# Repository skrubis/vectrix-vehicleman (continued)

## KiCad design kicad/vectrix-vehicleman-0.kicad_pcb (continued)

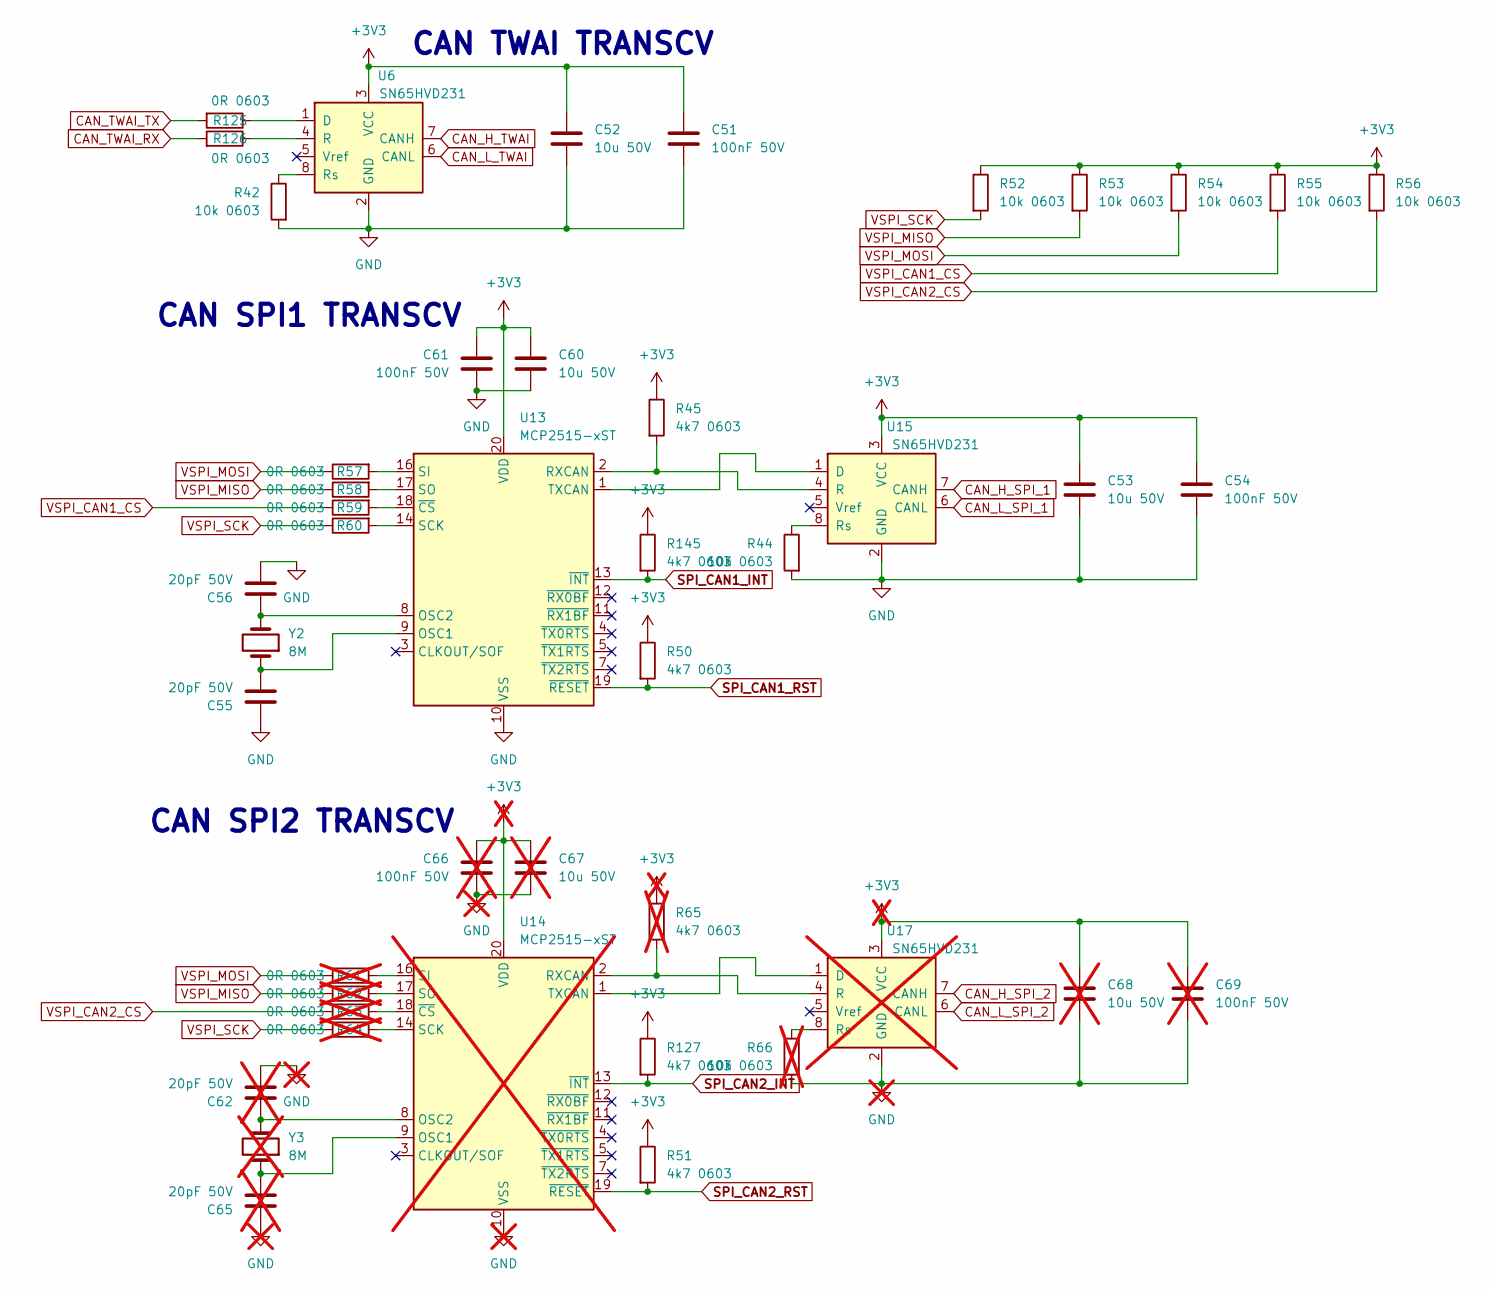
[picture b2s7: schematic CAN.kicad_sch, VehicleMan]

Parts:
C51, C54, C61: 100nF 50V; C_0603_1608Metric; LCSC C14663
C52, C53, C60: 10u 50V; C_1206_3216Metric; LCSC C13585
C55, C56: 20pF 50V; C_0603_1608Metric; LCSC C105621
C62, C65: 20pF 50V; C_0603_1608Metric; LCSC C105621; not fitted
C66, C69: 100nF 50V; C_0603_1608Metric; LCSC C14663; not fitted
C67, C68: 10u 50V; C_1206_3216Metric; LCSC C13585; not fitted
R42, R44, R52, R53, R54, R55, R56: 10k 0603; R_0603_1608Metric; LCSC C2930027
R45, R50, R51, R127, R145: 4k7 0603; R_0603_1608Metric; LCSC C99782
R57, R58, R59, R60, R125, R126: 0R 0603; R_0603_1608Metric; LCSC C21189
R61, R62, R63, R64: 0R 0603; R_0603_1608Metric; LCSC C21189; not fitted
R65: 4k7 0603; R_0603_1608Metric; LCSC C99782; not fitted
R66: 10k 0603; R_0603_1608Metric; LCSC C2930027; not fitted
U6, U15: SN65HVD231; SOIC-8_3.9x4.9mm_P1.27mm; LCSC C12084
U13: MCP2515-xST; TSSOP-20_4.4x6.5mm_P0.65mm; LCSC C185941
U14: MCP2515-xST; TSSOP-20_4.4x6.5mm_P0.65mm; LCSC C185941; not fitted
U17: SN65HVD231; SOIC-8_3.9x4.9mm_P1.27mm; LCSC C12084; not fitted
Y2: 8M; Crystal_SMD_HC49-SD
Y3: 8M; Crystal_SMD_HC49-SD; not fitted

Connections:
+3V3: C51.1, C52.1, C53.1, C54.1, C60.1, C61.1, C66.1, C67.1, C68.1, C69.1, R45.1, R50.1, R51.1, R52.1, R53.1, R54.1, R55.1, R56.1, R65.1, R127.1, R145.1, U6.3 (VCC), U13.20 (VDD), U14.20 (VDD), U15.3 (VCC), U17.3 (VCC); also elsewhere on the board
CAN_H_SPI_1: U15.7 (CANH); also elsewhere on the board
CAN_H_SPI_2: U17.7 (CANH); also elsewhere on the board
CAN_H_TWAI: U6.7 (CANH); also elsewhere on the board
CAN_L_SPI_1: U15.6 (CANL); also elsewhere on the board
CAN_L_SPI_2: U17.6 (CANL); also elsewhere on the board
CAN_L_TWAI: U6.6 (CANL); also elsewhere on the board
CAN_TWAI_RX: R126.2; also elsewhere on the board
CAN_TWAI_TX: R125.2; also elsewhere on the board
GND: C51.2, C52.2, C53.2, C54.2, C55.1, C56.2, C60.2, C61.2, C62.2, C65.1, C66.2, C67.2, C68.2, C69.2, R42.2, R44.2, R66.2, U6.2 (GND), U13.10 (VSS), U14.10 (VSS), U15.2 (GND), U17.2 (GND); also elsewhere on the board
unnamed: R125.1, U6.1 (D)
unnamed: R126.1, U6.4 (R)
unnamed: R42.1, U6.8 (Rs)
unnamed: C55.2, U13.9 (OSC1), Y2.1
unnamed: C56.1, U13.8 (OSC2), Y2.2
unnamed: R45.2, U13.2 (RXCAN), U15.4 (R)
unnamed: R60.2, U13.14 (SCK)
unnamed: R57.2, U13.16 (SI)
unnamed: R58.2, U13.17 (SO)
unnamed: U13.1 (TXCAN), U15.1 (D)
unnamed: R59.2, U13.18 (~CS)
unnamed: C65.2, U14.9 (OSC1), Y3.1
unnamed: C62.1, U14.8 (OSC2), Y3.2
unnamed: R65.2, U14.2 (RXCAN), U17.4 (R)
unnamed: R64.2, U14.14 (SCK)
unnamed: R61.2, U14.16 (SI)
unnamed: R62.2, U14.17 (SO)
unnamed: U14.1 (TXCAN), U17.1 (D)
unnamed: R63.2, U14.18 (~CS)
unnamed: R44.1, U15.8 (Rs)
unnamed: R66.1, U17.8 (Rs)
SPI_CAN1_INT: R145.2, U13.13 (~INT); also elsewhere on the board
SPI_CAN1_RST: R50.2, U13.19 (~RESET); also elsewhere on the board
SPI_CAN2_INT: R127.2, U14.13 (~INT); also elsewhere on the board
SPI_CAN2_RST: R51.2, U14.19 (~RESET); also elsewhere on the board
VSPI_CAN1_CS: R55.2, R59.1; also elsewhere on the board
VSPI_CAN2_CS: R56.2, R63.1; also elsewhere on the board
VSPI_MISO: R53.2, R58.1, R62.1; also elsewhere on the board
VSPI_MOSI: R54.2, R57.1, R61.1; also elsewhere on the board
VSPI_SCK: R52.2, R60.1, R64.1; also elsewhere on the board

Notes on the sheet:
CAN SPI2 TRANSCV
CAN SPI1 TRANSCV
CAN TWAI TRANSCV

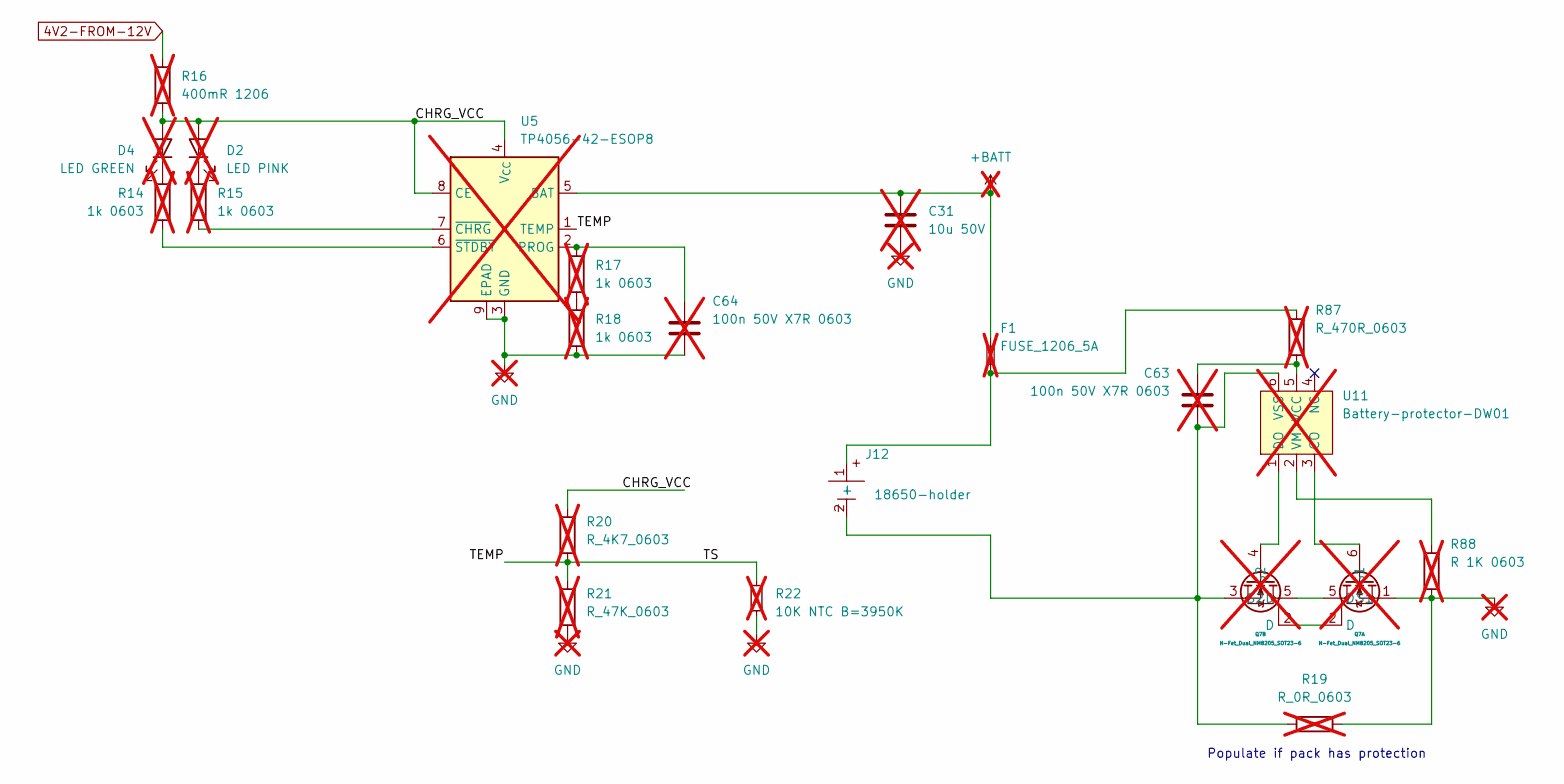
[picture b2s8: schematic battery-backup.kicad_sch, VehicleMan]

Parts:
C31: 10u 50V; C_1206_3216Metric; LCSC C13585; not fitted
C63, C64: 100n 50V X7R 0603; C_0603_1608Metric; LCSC C314282; not fitted
D2: LED PINK; LED_0805_2012Metric; LCSC C965821; not fitted
D4: LED GREEN; LED_0805_2012Metric; LCSC C5875740; not fitted
F1: FUSE_1206_5A; Fuse_1206_3216Metric; LCSC C883136; not fitted
J12: 18650-holder; C5290175-18650-holder; LCSC C5290175
Q7: N-Fet_Dual_NM8205_SOT23-6; SOT-23-6; LCSC C5156806; not fitted
R14, R15, R17, R18: 1k 0603; R_0603_1608Metric; LCSC C2907113; not fitted
R16: 400mR 1206; R_1206_3216Metric; LCSC C912792; not fitted
R19: R_0R_0603; R_0603_1608Metric; LCSC C2907080; not fitted
R20: R_4K7_0603; R_0603_1608Metric; LCSC C23162; not fitted
R21: R_47K_0603; R_0603_1608Metric; LCSC C2907173; not fitted
R22: 10K NTC B=3950K; R_0603_1608Metric; LCSC C279936; not fitted
R87: R_470R_0603; R_0603_1608Metric; LCSC C2907172; not fitted
R88: R 1K 0603; R_0603_1608Metric; LCSC C25585; not fitted
U5: TP4056-42-ESOP8; SOIC-8-1EP_3.9x4.9mm_P1.27mm_EP2.41x3.3mm_ThermalVias; not fitted
U11: Battery-protector-DW01; SOT-23-6; LCSC C917079; not fitted

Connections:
4V2-FROM-12V: R16.1; also elsewhere on the board
+BATT: C31.1, F1.2, U5.5 (BAT); also elsewhere on the board
/Battery/CHRG_VCC: D2.2 (A), D4.2 (A), R16.2, R20.1, U5.4 (V_{CC}), U5.8 (CE)
/Battery/TEMP: R20.2, R21.1, R22.1, U5.1 (TEMP)
GND: C31.2, C64.2, Q7.1 (S1), R18.2, R19.2, R21.2, R22.2, R88.2, U5.3 (GND), U5.9 (EPAD); also elsewhere on the board
unnamed: D2.1 (K), R15.1
unnamed: D4.1 (K), R14.1
unnamed: F1.1, J12.1 (+), R87.1
unnamed: C63.2, J12.2 (-), Q7.3 (S2), R19.1, U11.6 (VSS)
unnamed: Q7.6 (G1), U11.3 (CO)
unnamed: Q7.4 (G2), U11.1 (DO)
unnamed: R17.2, R18.1
unnamed: C64.1, R17.1, U5.2 (PROG)
unnamed: R15.2, U5.7 (~CHRG)
unnamed: R14.2, U5.6 (~STDBY)
unnamed: C63.1, R87.2, U11.5 (VCC)
unnamed: R88.1, U11.2 (VM)

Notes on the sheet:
Populate if pack has protection

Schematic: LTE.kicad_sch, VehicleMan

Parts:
C30, C71, C90, C94: 10u 50V; C_1206_3216Metric; LCSC C13585
C70, C100: Tant 47u 17V; CP_EIA-3528-12_Kemet-T; LCSC C136751
C79, C80, C81: 33pF 0603; C_0603_1608Metric; LCSC C107047
C87, C88, C89, C98: 100nF 50V; C_0603_1608Metric; LCSC C14663
C93, C95: 33pF 0402; C_0402_1005Metric; LCSC C1562; not fitted
C96: 33pF 0402; C_0402_1005Metric; LCSC C1562
D1: TPESD1P0RFW; SOT-323_SC-70; LCSC C521956
D18: LED GREEN; LED_0805_2012Metric; LCSC C5875740
D19: LED PINK; LED_0805_2012Metric; LCSC C965821
D26: PESD5V0L4UG; SOT-353_SC-70-5; LCSC C5116450
FB4, FB5: FB_100R_2.5A; L_0603_1608Metric; LCSC C96995
J8: SIM_Card_Shielded; nanoSIM_Hinged_CUI_NSIM-2-C; LCSC C266890
J10: GPS U.FL; U.FL_Hirose_U.FL-R-SMT-1_Vertical; LCSC C496552
J11: LTE U.FL; U.FL_Hirose_U.FL-R-SMT-1_Vertical; LCSC C496552
L1: 47nH; L_0402_1005Metric; LCSC C97998
L6, L7: 27nH; L_0402_1005Metric; LCSC C12669; not fitted
Q12, Q13, Q14, Q15, Q18: MMBT3904; SOT-23
R8, R96, R97, R104: R_27R_0603; R_0603_1608Metric; LCSC C101313
R43, R67: 1k 0603; R_0603_1608Metric; LCSC C2907113
R70, R71, R124: 100k 0603; R_0603_1608Metric; LCSC C14675
R106: 0R 0603; R_0603_1608Metric; LCSC C21189; not fitted
R107, R115, R116, R117, R119, R120, R123, R130, R131, R133: 4k7 0603; R_0603_1608Metric; LCSC C99782
R118, R121, R122, R132: 0R 0603; R_0603_1608Metric; LCSC C21189
R128, R129, R143: 0R 0402; R_0402_1005Metric; LCSC C106231
R134, R135: 4k7 0603; R_0603_1608Metric; LCSC C99782; not fitted
R144: 10R 0402; R_0402_1005Metric; LCSC C22859
TP1, TP2, TP3: TestPoint; TestPoint_Pad_D1.0mm; not fitted
U18: SIM7070G; LCSC C2892847
U23: ME6217C33M5G; SOT-23-5; LCSC C427602

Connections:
+1V8: C94.1, C98.1, R115.1, R116.1, R117.1, R119.1, R120.1, R123.1, R135.2, U18.15 (VDD_EXT)
+3V3: R70.1, R71.1, R106.2, R107.1, R133.1; also elsewhere on the board
/LTE/GNSS_ANT: L6.1, R143.2, U18.53 (GNSS_ANT)
/LTE/GPS_VCC: C71.1, C88.1, R144.2, U23.5 (V_{OUT})
/LTE/LTE_ANT: R129.2, U18.60 (RF_ANT)
/LTE/LTE_GPIO5: Q18.2 (E), R134.2, R135.1, U18.48 (GPIO5/SPI_CS)
/LTE/POWERKEY: Q15.3 (C), R132.2
/LTE/SIM_CLK: C79.1, R97.2, U18.32 (SIM_CLK)
/LTE/SIM_DATA: R104.2, U18.31 (SIM_DATA)
/LTE/SIM_RST: C80.1, R96.2, U18.33 (SIM_RST)
/LTE/SIM_VDD: R8.2, U18.30 (SIM_VDD)
/LTE/UART1_DTR: Q14.3 (C), R118.2, R120.2
/LTE/UART1_RXD: Q13.3 (C), R117.2, R121.2
/LTE/UART1_TXD: Q12.2 (E), R122.2
GND: C30.2, C70.2, C71.2, C79.2, C80.2, C81.2, C87.2, C88.2, C89.2, C90.2, C93.1, C94.2, C95.1, C98.2, C100.2, D1.3 (A), D26.2 (A), J8.5 (GND), J8.SH, J10.2 (Ext), J11.2 (Ext), L6.2, L7.2, Q15.2 (E), R43.2, R67.2, R124.2, R130.1, R134.1, U18.2 (GND), U18.17 (GND), U18.18 (GND), U18.29 (GND), U18.39 (GND), U18.45 (GND), U18.46 (GND), U18.54 (GND), U18.58 (GND), U18.59 (GND), U18.61 (GND), U18.62 (GND), U18.63 (GND), U18.64 (GND), U18.65 (GND), U23.2 (V_{SS}); also elsewhere on the board
GPS_LDO_EN: R124.1, U23.3 (CE); also elsewhere on the board
LTE_DTR: Q14.2 (E), R71.2; also elsewhere on the board
LTE_GPIO5_HV: Q18.3 (C), R133.2; also elsewhere on the board
LTE_POWERKEY: R131.1; also elsewhere on the board
LTE_RX: Q13.2 (E), R70.2; also elsewhere on the board
LTE_TX: Q12.3 (C), R107.2; also elsewhere on the board
LTE_USB_VBUS_DET: U18.24 (USB_VBUS); also elsewhere on the board
unnamed: C93.2, R128.2, R129.1
unnamed: C96.2, L7.1, R143.1
unnamed: C30.1, C70.1, C87.1, C100.1, FB4.1, R106.1, U18.55 (VBAT), U18.56 (VBAT), U18.57 (VBAT)
unnamed: D18.2 (A), U18.66 (STATUS)
unnamed: D18.1 (K), R43.1
unnamed: D19.2 (A), U18.52 (NETLIGHT)
unnamed: D19.1 (K), R67.1
unnamed: D26.1 (K1), J8.2 (RST), R96.1
unnamed: D26.3 (K2), J8.3 (CLK), R97.1
unnamed: C81.1, D26.4 (K3), J8.7 (I/O), R104.1
unnamed: D26.5 (K4), J8.1 (VCC), R8.1
unnamed: C96.1, J10.1 (In), L1.1
unnamed: C95.2, D1.1 (K), D1.2 (K), J11.1 (In), R128.1
unnamed: L1.2, R144.1
unnamed: Q12.1 (B), R115.2
unnamed: Q13.1 (B), R116.2
unnamed: Q14.1 (B), R119.2
unnamed: Q15.1 (B), R130.2, R131.2
unnamed: Q18.1 (B), R123.2
unnamed: TP1.1, U18.6 (BOOT_CFG)
unnamed: TP2.1, U18.22 (DEBUG_RXD)
unnamed: TP3.1, U18.23 (DEBUG_TXD)
unnamed: R132.1, U18.1 (PWRKEY)
unnamed: R118.1, U18.3 (UART1_DTR)
unnamed: R121.1, U18.10 (UART1_RXD)
unnamed: R122.1, U18.9 (UART1_TXD)
unnamed: C89.1, C90.1, FB5.2, U23.1 (V_{IN})
USB_LTE_DN: U18.28 (USB_DM); also elsewhere on the board
USB_LTE_DP: U18.27 (USB_DP); also elsewhere on the board
VBUS: FB4.2, FB5.1; also elsewhere on the board

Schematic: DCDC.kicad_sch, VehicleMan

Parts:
C17, C18, C97, C99: 10u 50V; C_1206_3216Metric; LCSC C13585
C22, C23, C25, C32, C38: 100nF 50V; C_0603_1608Metric; LCSC C14663
C26, C29, C74, C82, C83, C91, C92: 10u 50V; C_1206_3216Metric; LCSC C13585; not fitted
C27, C28, C72, C73, C84: 100nF 50V; C_0603_1608Metric; LCSC C14663; not fitted
C37: 100uF 25V; CP_Elec_6.3x7.7; LCSC C2918360
C75: 100uF 25V; CP_Elec_6.3x7.7; LCSC C2918360; not fitted
D8: SMAJ18A; D_SMA
D9, D20, D41: Schottky 40V 10A; TO-277B; LCSC C2988031; not fitted
D21: D_Schottky_3A_40V; D_SMA; LCSC C2758580; not fitted
F9: Polyfuse 2A; Fuse_2920_7451Metric; LCSC C6165181
F16: Polyfuse 250V .4A; Fuse_Bourns_MF-RHT200; LCSC C693579
FB3: FB_100R_2.5A; L_0603_1608Metric; LCSC C96995; not fitted
L2: Inductor_3.3uH_4.7A_shielded; L_7.3x7.3_H4.5; LCSC C216194; not fitted
L3: 5.6uH 5.5A; L_KOHERelec_MDA7030; LCSC C475914
L4: 1uH 6A; L_APV_APH0412; LCSC C167203; not fitted
L5: 1uH 6A; L_APV_APH0412; LCSC C167203
Q3: AO3400A; SOT-23; LCSC C347475; not fitted
Q6, Q8: PMOS_30V_5.5A; SOT-23; LCSC C105162; not fitted
R5: 42.2k 0603; R_0603_1608Metric; LCSC C5126245
R6: 10k 0603; R_0603_1608Metric; LCSC C2930027
R10, R12, R13, R113, R114: 100k 0603; R_0603_1608Metric; LCSC C14675; not fitted
R11: 604k 0603; R_0603_1608Metric; LCSC C2933246; not fitted
R23: 100k 0603; R_0603_1608Metric; LCSC C14675
R24: 453k 0603; R_0603_1608Metric; LCSC C27009
R68: R_47K_0603; R_0603_1608Metric; LCSC C2907173; not fitted
R69: 10k 0603; R_0603_1608Metric; LCSC C2930027; not fitted
R108, R109, R110, R111: 0R 0603; R_0603_1608Metric; LCSC C21189
U2: TPS61022; Texas_RWU0007A_VQFN-7_2x2mm_P0.5mm; not fitted
U3: TPS62A02DRL; SOT-563
U4: TPS563300; SOT-583-8; LCSC C5219249
U7: GigaESC TL494OC 2.1.0
U19: BOOSTER_2A_12V_MAX_FP6291LR-G1; SOT-23-6; LCSC C18701; not fitted

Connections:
4V2-FROM-12V: C25.1, C97.1, C99.1, L3.2, Q6.3 (D), R5.1, R108.2, R109.2; also elsewhere on the board
4V2-FROM-BAT: C72.1, C91.1, C92.1, Q3.1 (G), Q6.1 (G), Q8.3 (D), R11.1, R12.2, U2.3 (VOUT)
12V_BATT: D20.1 (A), D20.2 (A), FB3.2
12V_HV: D41.1 (A), D41.2 (A), F9.1
+3V3: C37.1, C38.1, L5.2, R24.1; also elsewhere on the board
+12P: D9.1 (A), D9.2 (A), R110.1, R111.1; also elsewhere on the board
+12V: C17.1, C22.1, D9.3 (K), D20.3 (K), D41.3 (K), R110.2, R111.2, U4.3 (VIN); also elsewhere on the board
+BATT: C26.1, C27.1, L4.1, U2.5 (EN), U2.7 (VIN); also elsewhere on the board
GND: C17.2, C18.2, C22.2, C25.2, C26.2, C27.2, C28.2, C29.2, C32.2, C37.2, C38.2, C72.2, C73.2, C74.2, C75.2, C82.2, C83.2, C84.2, C91.2, C92.2, C97.2, C99.2, D8.2 (A2), Q3.2 (S), R6.2, R10.2, R12.1, R23.2, R68.2, R69.2, U2.1 (GND), U2.6 (MODE), U3.1 (GND), U3.6 (PG), U4.4 (GND), U7.3 (GND), U19.2 (GND); also elsewhere on the board
HV+: F16.1; also elsewhere on the board
unnamed: D8.1 (A1), F9.2, U7.1 (+12V)
unnamed: D21.2 (A), L2.2, U19.1 (LX)
unnamed: C73.1, C74.1, C75.1, D21.1 (K), FB3.1, R113.1
unnamed: Q3.3 (D), Q8.1 (G), R13.1
unnamed: R113.2, R114.1
unnamed: R10.1, R11.2, U2.4 (FB)
unnamed: L4.2, U2.2 (SW)
unnamed: R23.1, R24.2, U3.5 (FB)
unnamed: L5.1, U3.2 (SW)
unnamed: C23.1, U4.6 (BST)
unnamed: R5.2, R6.1, U4.8 (FB)
unnamed: C23.2, L3.1, U4.5 (SW)
unnamed: F16.2, U7.2 (HV)
unnamed: R69.1, R114.2, U19.3 (FB)
unnamed: R68.1, U19.6 (OC)
VBUS: C18.1, C28.1, C29.1, C32.1, C82.1, C83.1, C84.1, L2.1, Q6.2 (S), Q8.2 (S), R13.2, R108.1, R109.1, U3.3 (VIN), U3.4 (EN), U19.4 (EN), U19.5 (Vcc); also elsewhere on the board

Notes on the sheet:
BATT BOOST TO 4V2
1A trip
IF EXT PWR EXISTS - USE THAT IF NO EXT PWR EXISTS - USE BATT
https://github.com/kaminaris/GigaESC/tree/master/PowerBoard/TL494V2OC
4V2 ORING
https://webench.ti.com/appinfo/webench/scripts/SDP.cgi?ID=62C56A5871A9F317
MAIN TO 3V3
EXT12V TO 4V2
https://webench.ti.com/appinfo/webench/scripts/SDP.cgi?ID=FB38C6AE199D341B
BATT BOOST TO 12V
ext 12V

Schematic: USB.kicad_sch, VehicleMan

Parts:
CN1: SHOU-HAN-TYPE-C16PIN_C393939; USB_C_Receptacle_HCTL_HC-TYPE-C-16P-01A; LCSC C2765186
D27: PESD5V0L4UG; SOT-353_SC-70-5; LCSC C5116450
R100, R101: R_27R_0603; R_0603_1608Metric; LCSC C101313
R102, R103: R_5k1_0603; R_0603_1608Metric; LCSC C23186
R112: 0R 0603; R_0603_1608Metric; LCSC C21189
SW2: SW_DIP_x04; SW_DIP_SPSTx04_Slide_9.78x12.34mm_W7.62mm_P2.54mm; LCSC C99418

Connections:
GND: CN1.A1 (GND), CN1.A12 (GND), CN1.B1 (GND), CN1.B12 (GND), CN1.S1 (SHIELD), D27.2 (A), R102.2, R103.2; also elsewhere on the board
LTE_USB_VBUS_DET: D27.4 (K3), R112.1; also elsewhere on the board
unnamed: CN1.A5 (CC1), R102.1
unnamed: CN1.B5 (CC2), R103.1
unnamed: CN1.A4 (VBUS), CN1.A9 (VBUS), CN1.B4 (VBUS), CN1.B9 (VBUS), R112.2
unnamed: CN1.A6 (D+), CN1.B6 (D+), D27.1 (K1), R100.1
unnamed: CN1.A7 (D-), CN1.B7 (D-), D27.3 (K2), R101.1
unnamed: R100.2, SW2.2, SW2.4
unnamed: R101.2, SW2.1, SW2.3
USB_DN: SW2.6; also elsewhere on the board
USB_DP: SW2.5; also elsewhere on the board
USB_LTE_DN: SW2.8; also elsewhere on the board
USB_LTE_DP: SW2.7; also elsewhere on the board

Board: 2 copper layers, 405 parts (0 on the bottom side), 241 nets, no tracks yet.

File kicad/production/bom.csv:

Designator,Footprint,Quantity,Value,LCSC Part #
BT1,BatteryHolder_MYOUNG_BS-07-A1BJ001_CR2032,1,Battery_Cell,C2979167
"C100, C70",CP_EIA-3528-12_Kemet-T,2,Tant 47u 17V,C136751
"C11, C12, C13, C14, C16, C22, C23, C25, C32, C33, C38, C47, C48, C49, C50, C51, C54, C57, C58, C59, C61, C76, C77, C87, C88, C89, C98",0603,27,100nF 50V,C14663
"C17, C18, C20, C21, C30, C52, C53, C60, C71, C78, C8, C9, C90, C94, C97, C99",1206,16,10u 50V,C13585
C19,0603,1,1uF 50V,C6119852
C34,1206,1,1nF 2kV 1206,C9196
"C35, C36, C39, C40, C79, C80, C81",0603,7,33pF 0603,C107047
C37,CP_Elec_6.3x7.7,1,100uF 25V, C2918360
"C55, C56",0603,2,20pF 50V,C105621
C96,0402,1,33pF 0402,C1562
CN1,USB_C_Receptacle_HCTL_HC-TYPE-C-16P-01A,1,SHOU-HAN-TYPE-C16PIN_C393939,C2765186
D1,SOT-323_SC-70,1,TPESD1P0RFW,C521956
"D10, D6",D_SMA,2,SMAJ15CA,C2848698
"D11, D5",D_SMA,2,SMAJ6.0CA,C134999
"D12, D7",D_SOD-323,2,D_TVS,C41409313
"D16, D40",D_SOD-128,2,D_Schottky_5A_360mV@5A,C50603
"D17, D3, D8",D_SMA,3,SMAJ18A,
"D18, D25",0805,2,LED GREEN,C5875740
D19,0805,1,LED PINK,C965821
"D22, D28, D37, D38, D39",D_SOD-123,5,TPSMF12A,C42440530
"D23, D33, D34",D_SOD-123,3,1N4148W,C917030
D24,SOT-23,1,PSM712-ES,C5180294
"D26, D27, D42",SOT-353_SC-70-5,3,PESD5V0L4UG,C5116450
"D29, D31",D_SMA,2,1N4001,C727081
"F10, F11, F12, F13, F14, F15",1812,6,Polyfuse 1.5A,C883154
F16,Fuse_Bourns_MF-RHT200,1,Polyfuse 250V .4A,C693579
"F2, F9",2920,2,Polyfuse 2A,C6165181
"F3, F4, F5, F6",1812,4,Polyfuse 140mA 60V,C20994
"F32, F33",0805,2,200mA PTC,C2840556
"FB4, FB5",0603,2,FB_100R_2.5A,C96995
"GD2, GD3, GD4, GD7",1812,4,GDT_2Pin,C9235
J1,"TerminalBlock_Phoenix_MKDS-1,5-2-5.08_1x02_P5.08mm_Horizontal",1,Screw_Terminal_01x02,C8465
J10,U.FL_Hirose_U.FL-R-SMT-1_Vertical,1,GPS U.FL,C496552
J11,U.FL_Hirose_U.FL-R-SMT-1_Vertical,1,LTE U.FL,C496552
J12,C5290175-18650-holder,1,18650-holder,C5290175
J17,TerminalBlock_4Ucon_1x02_P3.50mm_Horizontal,1,SW1,C695629
J18,TerminalBlock_4Ucon_1x02_P3.50mm_Horizontal,1,SW2,C695629
J19,TerminalBlock_4Ucon_1x02_P3.50mm_Horizontal,1,SW3,C695629
J20,TerminalBlock_4Ucon_1x02_P3.50mm_Horizontal,1,SW4,C695629
"J22, J3",TerminalBlock_4Ucon_1x03_P3.50mm_Horizontal,2,CAN 0, C695630
J23,TerminalBlock_4Ucon_1x03_P3.50mm_Horizontal,1,PWR_OUT, C695630
J24,TerminalBlock_4Ucon_1x03_P3.50mm_Horizontal,1,PWR, C695630
J25,TerminalBlock_4Ucon_1x03_P3.50mm_Horizontal,1,K1, C695630
J26,TerminalBlock_4Ucon_1x02_P3.50mm_Horizontal,1,K1,C695629
J27,TerminalBlock_4Ucon_1x03_P3.50mm_Horizontal,1,K2, C695630
J28,TerminalBlock_4Ucon_1x02_P3.50mm_Horizontal,1,K2,C695629
J5,TerminalBlock_4Ucon_1x03_P3.50mm_Horizontal,1,CAN SPI1, C695630
J8,nanoSIM_Hinged_CUI_NSIM-2-C,1,SIM_Card_Shielded,C266890
J9,TerminalBlock_4Ucon_1x02_P3.50mm_Horizontal,1,CP PP,C695629
"K1, K2",Relay_DPDT_Omron_G2RL-2,2,G2RL-24 DC5,C6866153
L1,0402,1,47nH,C97998
L3,L_KOHERelec_MDA7030,1,5.6uH 5.5A,C475914
L5,L_APV_APH0412,1,1uH 6A,C167203
MICRO_SD1,TF-01A,1,TF-01A,C91145
"PF1, PF2, PF3",1206,3,250mA,C70065
"Q1, Q2",SOT-23,2,BSS138,C112239
"Q10, Q11, Q5, Q9",SOT-23,4,BSS138-7-F,C40912
"Q12, Q13, Q14, Q15, Q18",SOT-23,5,MMBT3904,
"Q16, Q17",SOT-23,2,Q_NPN_BEC,C460141
"Q19, Q20, Q21, Q22",SOT-23,4,PMOS_30V_5.5A,C105162
Q4,SOT-23,1,Q_PMOS_30V_5.5A_SOT23,C105162
R1,0603,1,56k 0603,C23206
"R100, R101, R104, R8, R96, R97",0603,6,R_27R_0603,C101313
"R102, R103",0603,2,R_5k1_0603,C23186
"R105, R140, R141, R142, R25, R26, R31, R42, R44, R52, R53, R54, R55, R56, R6, R7",0603,16,10k 0603,C2930027
"R107, R115, R116, R117, R119, R120, R123, R127, R130, R131, R133, R136, R138, R145, R40, R41, R45, R50, R51, R78, R81, R84, R89, R98, R99",0603,25,4k7 0603,C99782
"R108, R109, R112, R118, R121, R122, R125, R126, R132, R33, R57, R58, R59, R60, R72, R9",0603,16,0R 0603,C21189
"R124, R23, R70, R71, R73, R74, R75",0603,7,100k 0603,C14675
"R128, R129, R143",0402,3,0R 0402,C106231
"R137, R139",0603,2,1.2k 0603,C114605
R144,0402,1,10R 0402,C22859
"R160, R161, R162, R163, R164, R167",0603,6,470R 0603,C23179
R24,0603,1,453k 0603,C27009
R27,0805,1,1M 0805,C17514
R29,0603,1,604k 0603,C2933246
"R30, R46, R47, R48, R49, R5",0603,6,42.2k 0603,C5126245
"R36, R37, R38, R94, R95",0603,5,120R 0603,C22787
"R4, R76, R79, R82, R85, R90, R92, R93",0603,8,150R 0603,C2907103
"R43, R67, R86",0603,3,1k 0603,C2907113
"R77, R80, R91",0603,3,2k7 0603,C13167
R83,0603,1,270R 0603,C22966
SW1,SW_PUSH_6mm,1,SW_Push,C455095
SW2,SW_DIP_SPSTx04_Slide_9.78x12.34mm_W7.62mm_P2.54mm,1,SW_DIP_x04, C99418
U1,ESP32-WROOM-32D,1,ESP32-WROOM-32E-R2,C82899
U10,SOIC-16_3.9x9.9mm_P1.27mm,1,CH340C,C84681
U12,Texas_PWSON-N6,1,HDC1080,C82227
U13,TSSOP-20_4.4x6.5mm_P0.65mm,1,MCP2515-xST,C185941
"U15, U6",SOIC-8_3.9x4.9mm_P1.27mm,2,SN65HVD231,C12084
U16,SOT-23-6,1,TPS3808DBV,C19653
U18,SIM7070G,1,SIM7070G,C2892847
U20,SOT-23-5,1,LM321,C668208
U21,SOIC-8_3.9x4.9mm_P1.27mm,1,DS1307Z+,C9868
U22,SOIC-28W_7.5x17.9mm_P1.27mm,1,MCP23017_SO,C629440
U23,SOT-23-5,1,ME6217C33M5G,C427602
U3,SOT-563,1,TPS62A02DRL,
U38,SMDIP-4_W7.62mm,1,PC817B,C66405
U4,SOT-583-8,1,TPS563300,C5219249
U7,GigaESC TL494OC 2.1.0,1,~,C157993
U8,LGA-16_3x3mm_P0.5mm_LayoutBorder3x5y,1,LIS3DH,C15134
U9,LGA-14_3x2.5mm_P0.5mm_LayoutBorder3x4y,1,LSM6DS3,C967633
Y2,Crystal_SMD_HC49-SD,1,8M,
Y4,Crystal_DS26_D2.0mm_L6.0mm_Horizontal,1,Crystal,C511702

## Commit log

2025-03-02 cleanup
2025-03-04 sch done-ish
2025-03-05 updated sch
2025-03-06 bom cleanup
